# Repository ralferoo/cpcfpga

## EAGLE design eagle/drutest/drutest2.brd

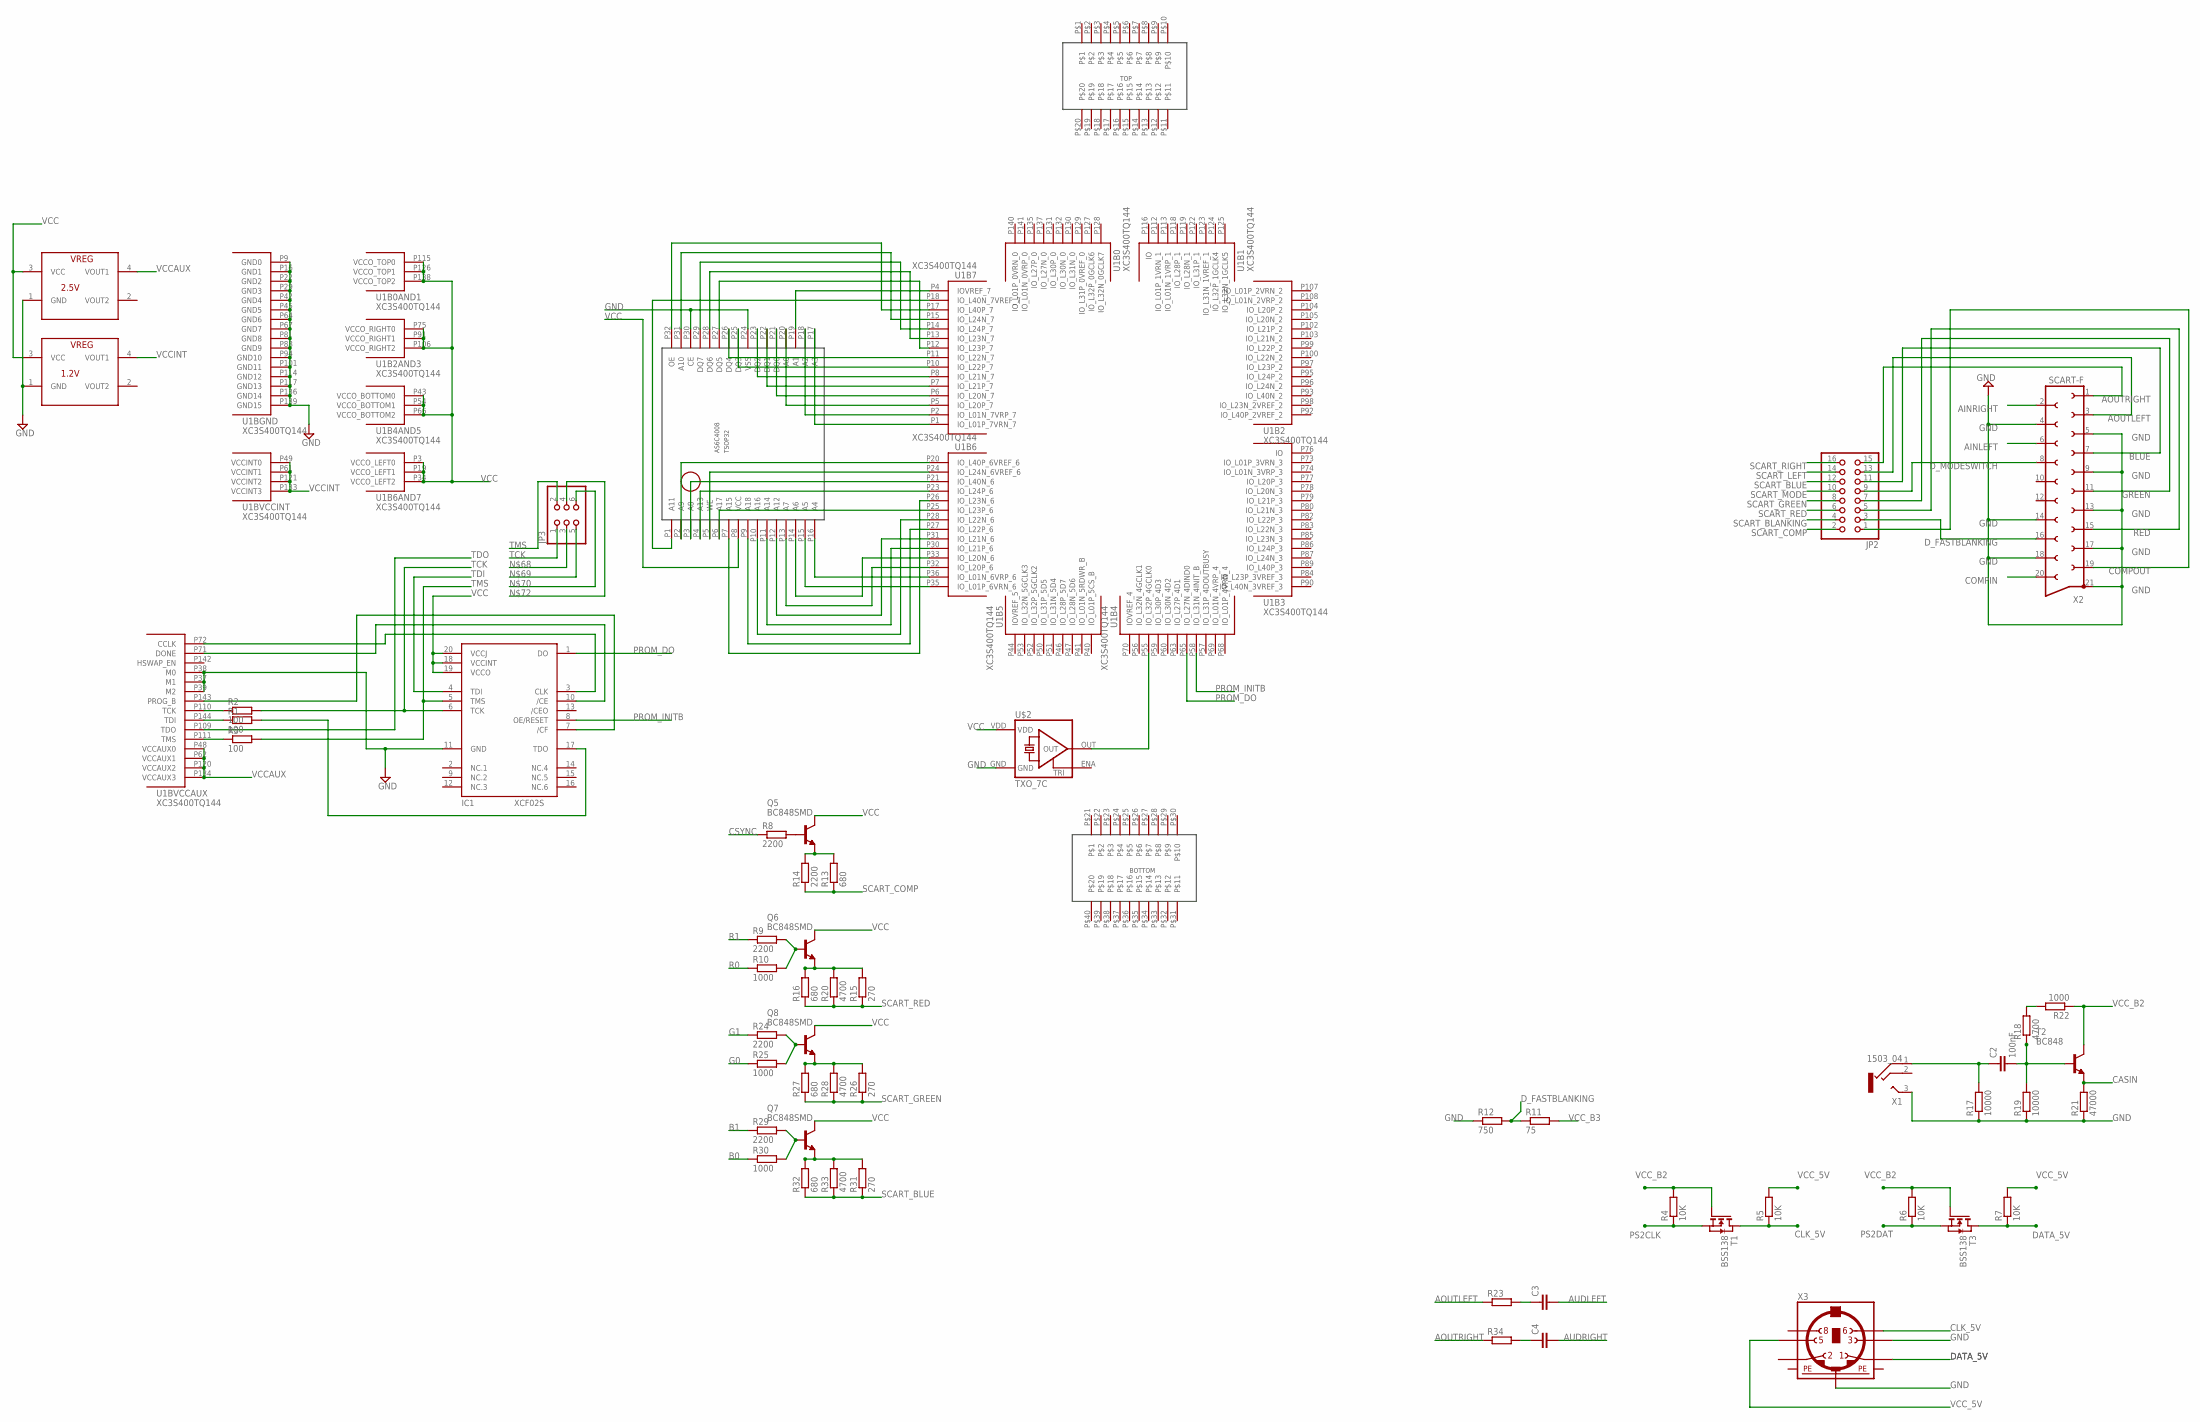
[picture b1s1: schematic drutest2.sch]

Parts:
C2: 100nF; C0603
C3, C4: C-EUC0603; C0603
IC1: XCF02S; VO20
JP2: PINHD-2X8; 2X08
JP3: PINHD-2X3; 2X03
Q5, Q6, Q7, Q8: BC848SMD; SOT23
R1, R2, R3: 100; R0805
R4, R5, R6, R7: 10K; R0805
R8, R9, R14, R24, R29: 2200; R0805
R10, R22, R25, R30: 1000; R0805
R11: 75; R0805
R12: 750; R0805
R13, R16, R27, R32: 680; R0805
R15, R26, R31: 270; R0805
R17, R19: 10000; R0805
R18, R20, R28, R33: 4700; R0805
R21: 47000; R0805
R23, R34: R-EU_M0805; M0805
T1, T3: BSS138; SOT-23
T2: BC848; SOT23
U1: XC3S400TQ144; TQ144
U$1: AS6C4008; TSOP32
U$2: TXO_7C; OSC_7C
U$3: 2.5V; SOT223
U$4: 1.2V; SOT223
U$5: EXPHDR
X1: 1503_04
X2: SCART-F
X3: MINI_DIN_6; M_DIN6

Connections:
AINLEFT: X2.6
AINRIGHT: X2.2
AOUTLEFT: JP2.13, R23.1, X2.3
AOUTRIGHT: JP2.15, R34.1, X2.1
AUDLEFT: C3.2
AUDRIGHT: C4.2
B0: R30.1
B1: R29.1
BLUE: JP2.11, X2.7
CASIN: R21.2, T2.2 (E)
CLK_5V: R5.1, T1.1 (D), X3.6
COMPIN: X2.20
COMPOUT: JP2.1, X2.19
CSYNC: R8.1
DATA_5V: R7.1, T3.1 (D), X3.1
D_FASTBLANKING: JP2.3, R11.1, R12.2, X2.16
D_MODESWITCH: JP2.9, X2.8
G0: R25.1
G1: R24.1
GND: IC1.11 (GND), R12.1, R17.1, R19.1, R21.1, U1.P9 (GND0), U1.P16 (GND1), U1.P22 (GND2), U1.P29 (GND3), U1.P37 (M1), U1.P38 (M0), U1.P39 (M2), U1.P42 (GND4), U1.P45 (GND5), U1.P64 (GND6), U1.P67 (GND7), U1.P81 (GND8), U1.P88 (GND9), U1.P94 (GND10), U1.P101 (GND11), U1.P114 (GND12), U1.P117 (GND13), U1.P136 (GND14), U1.P139 (GND15), U$1.P24 (VSS), U$1.P30 (CE), U$2.GND, U$3.1 (GND), U$4.1 (GND), X1.3 (2), X2.4, X2.5, X2.9, X2.13, X2.14, X2.17, X2.18, X2.21, X3.3, X3.SH2 (PE2)
GREEN: JP2.7, X2.11
unnamed: U1.P1 (IO_L01P_7VRN_7), U$1.P17 (A3)
unnamed: U1.P2 (IO_L01N_7VRP_7), U$1.P18 (A2)
unnamed: U1.P4 (IOVREF_7), U$1.P19 (A1)
unnamed: U1.P5 (IO_L20P_7), U$1.P20 (A0)
unnamed: U1.P6 (IO_L20N_7), U$1.P21 (DQ0)
unnamed: U1.P7 (IO_L21P_7), U$1.P22 (DQ1)
unnamed: U1.P8 (IO_L21N_7), U$1.P23 (DQ2)
unnamed: U1.P10 (IO_L22P_7), U$1.P25 (DQ3)
unnamed: U1.P11 (IO_L22N_7), U$1.P26 (DQ4)
unnamed: U1.P12 (IO_L23P_7), U$1.P27 (DQ5)
unnamed: U1.P13 (IO_L23N_7), U$1.P28 (DQ6)
unnamed: U1.P14 (IO_L24P_7), U$1.P29 (DQ7)
unnamed: U1.P15 (IO_L24N_7), U$1.P31 (A10)
unnamed: U1.P17 (IO_L40P_7), U$1.P32 (OE)
unnamed: U1.P18 (IO_L40N_7VREF_7), U$1.P1 (A11)
unnamed: U1.P20 (IO_L40P_6VREF_6), U$1.P2 (A9)
unnamed: U1.P21 (IO_L40N_6), U$1.P3 (A8)
unnamed: U1.P23 (IO_L24P_6), U$1.P4 (A13)
unnamed: U1.P24 (IO_L24N_6VREF_6), U$1.P5 (WE)
unnamed: U1.P25 (IO_L23P_6), U$1.P6 (A17)
unnamed: U1.P26 (IO_L23N_6), U$1.P7 (A15)
unnamed: U1.P27 (IO_L22P_6), U$1.P9 (A18)
unnamed: U1.P28 (IO_L22N_6), U$1.P10 (A16)
unnamed: U1.P30 (IO_L21P_6), U$1.P11 (A14)
unnamed: U1.P31 (IO_L21N_6), U$1.P12 (A12)
unnamed: U1.P32 (IO_L20P_6), U$1.P13 (A7)
unnamed: U1.P33 (IO_L20N_6), U$1.P14 (A6)
unnamed: U1.P35 (IO_L01P_6VRN_6), U$1.P15 (A5)
unnamed: U1.P36 (IO_L01N_6VRP_6), U$1.P16 (A4)
unnamed: IC1.3 (CLK), U1.P72 (CCLK)
unnamed: IC1.17 (TDO), R1.2
unnamed: IC1.10 (/CE), U1.P71 (DONE)
unnamed: R2.1, U1.P110 (TCK)
unnamed: IC1.7 (/CF), U1.P143 (PROG_B)
unnamed: R1.1, U1.P144 (TDI)
unnamed: R3.1, U1.P111 (TMS)
unnamed: Q6.1 (B), R9.2, R10.2
unnamed: Q6.2 (E), R15.2, R16.2, R20.2
unnamed: Q8.1 (B), R24.2, R25.2
unnamed: Q8.2 (E), R26.2, R27.2, R28.2
unnamed: Q7.1 (B), R29.2, R30.2
unnamed: Q7.2 (E), R31.2, R32.2, R33.2
unnamed: Q5.2 (E), R13.2, R14.2
unnamed: C2.2, R18.1, R19.2, T2.1 (B)
unnamed: C2.1, R17.2, X1.1
unnamed: R18.2, R22.2
unnamed: Q5.1 (B), R8.2
unnamed: C3.1, R23.2
unnamed: C4.1, R34.2
unnamed: U1.P55 (IO_L32P_4GCLK0), U$2.OUT
PE1: X3.SH1 (PE1)
PE3: X3.SH3 (PE3)
PROM_DO: IC1.1 (DO), U1.P65 (IO_L27N_4DIND0)
PROM_INITB: IC1.8 (OE/RESET), U1.P58 (IO_L31N_4INIT_B)
PS2CLK: R4.1, T1.2 (S)
PS2DAT: R6.1, T3.2 (S)
R0: R10.1
R1: R9.1
RED: JP2.5, X2.15
SCART_BLANKING: JP2.4
SCART_BLUE: JP2.12, R31.1, R32.1, R33.1
SCART_COMP: JP2.2, R13.1, R14.1
SCART_GREEN: JP2.8, R26.1, R27.1, R28.1
SCART_LEFT: JP2.14
SCART_MODE: JP2.10
SCART_RED: JP2.6, R15.1, R16.1, R20.1
SCART_RIGHT: JP2.16
TCK: IC1.6 (TCK), JP3.1, R2.2
TDI: IC1.4 (TDI)
TDO: U1.P109 (TDO)
TMS: IC1.5 (TMS), JP3.2, R3.2
VCC: IC1.18 (VCCINT), IC1.19 (VCCO), IC1.20 (VCCJ), Q5.3 (C), Q6.3 (C), Q7.3 (C), Q8.3 (C), U1.P3 (VCCO_LEFT0), U1.P19 (VCCO_LEFT1), U1.P34 (VCCO_LEFT2), U1.P43 (VCCO_BOTTOM0), U1.P54 (VCCO_BOTTOM1), U1.P66 (VCCO_BOTTOM2), U1.P75 (VCCO_RIGHT0), U1.P91 (VCCO_RIGHT1), U1.P106 (VCCO_RIGHT2), U1.P115 (VCCO_TOP0), U1.P126 (VCCO_TOP1), U1.P138 (VCCO_TOP2), U$1.P8 (VCC), U$2.VDD, U$3.3 (VCC), U$4.3 (VCC)
VCCAUX: U1.P48 (VCCAUX0), U1.P62 (VCCAUX1), U1.P120 (VCCAUX2), U1.P134 (VCCAUX3), U$3.4 (VOUT1)
VCCINT: U1.P49 (VCCINT0), U1.P61 (VCCINT1), U1.P121 (VCCINT2), U1.P133 (VCCINT3), U$4.4 (VOUT1)
VCC_5V: R5.2, R7.2, X3.5
VCC_B2: R4.2, R6.2, R22.1, T1.3 (G), T2.3 (C), T3.3 (G)
VCC_B3: R11.2

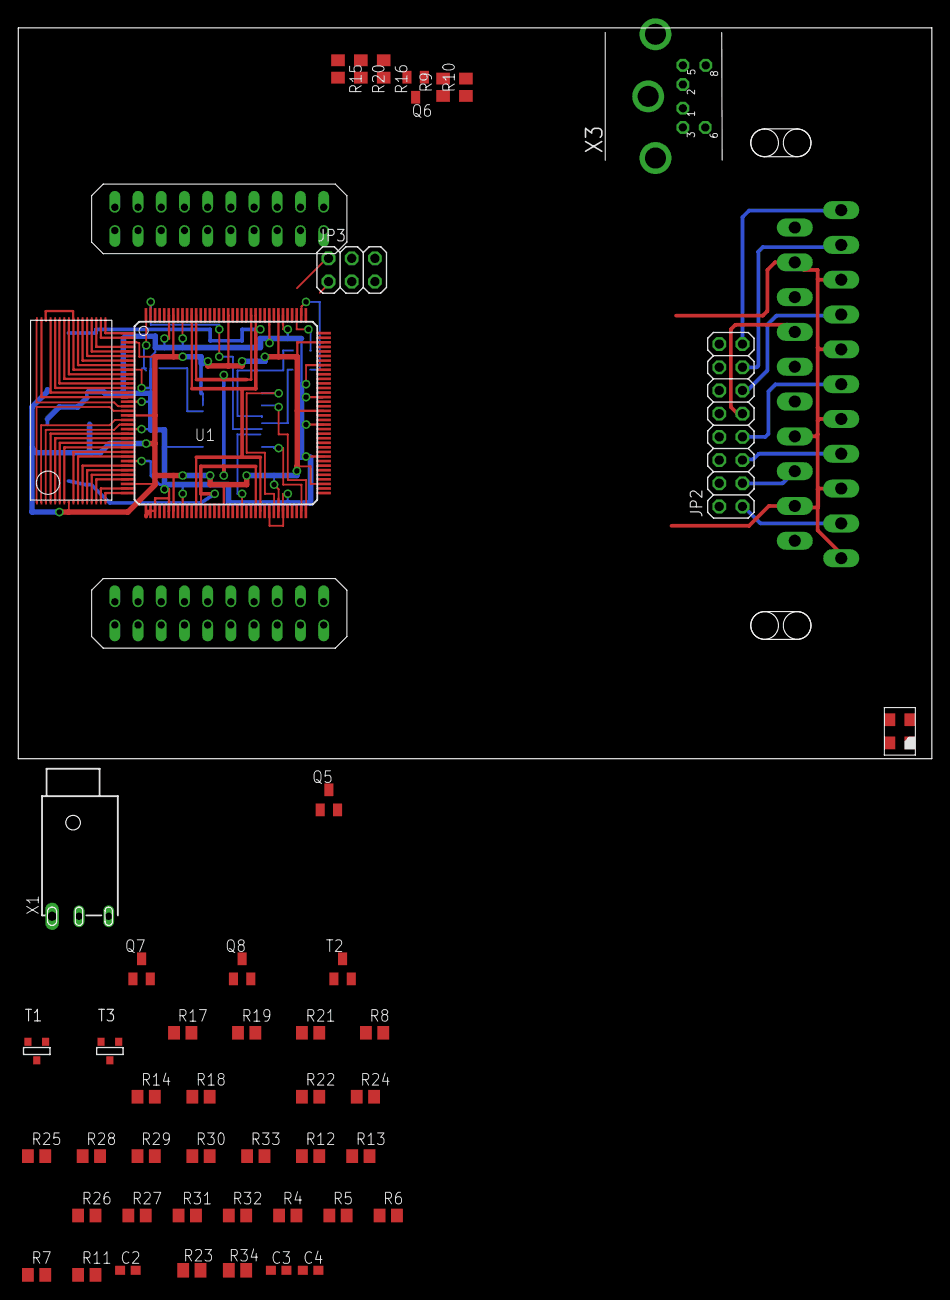
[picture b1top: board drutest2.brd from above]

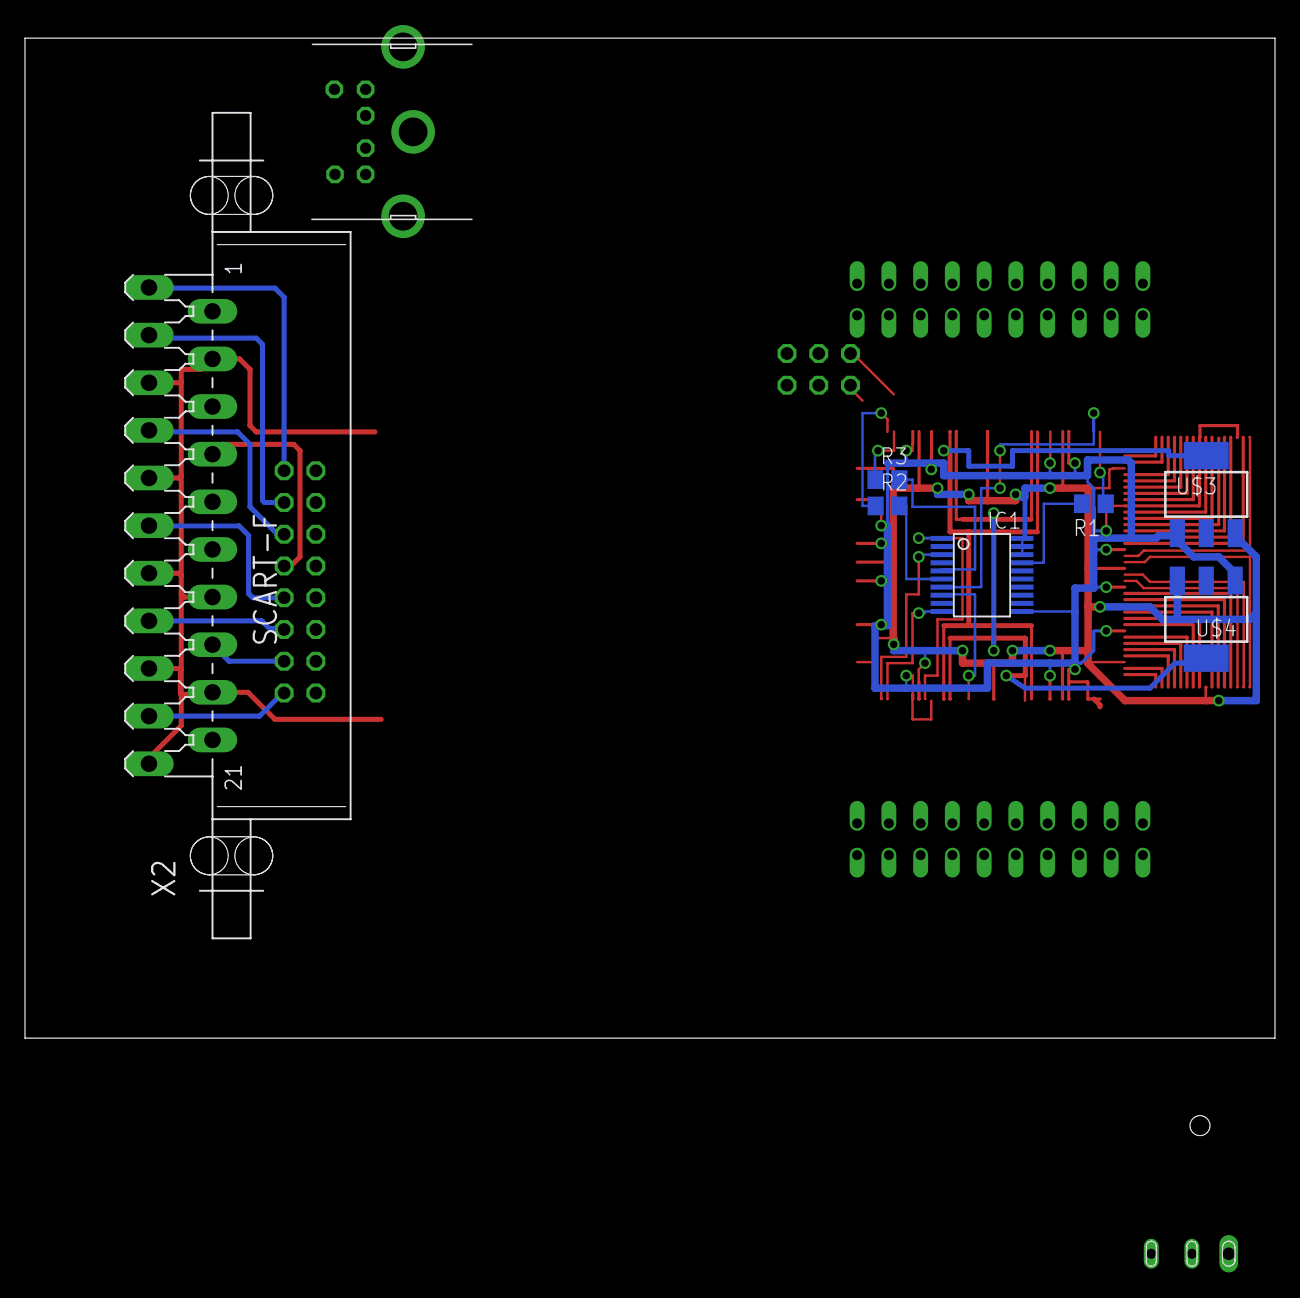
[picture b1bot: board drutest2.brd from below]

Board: 2 copper layers, 100.0 x 98.2 mm, 56 parts (7 on the bottom side), 77 nets.

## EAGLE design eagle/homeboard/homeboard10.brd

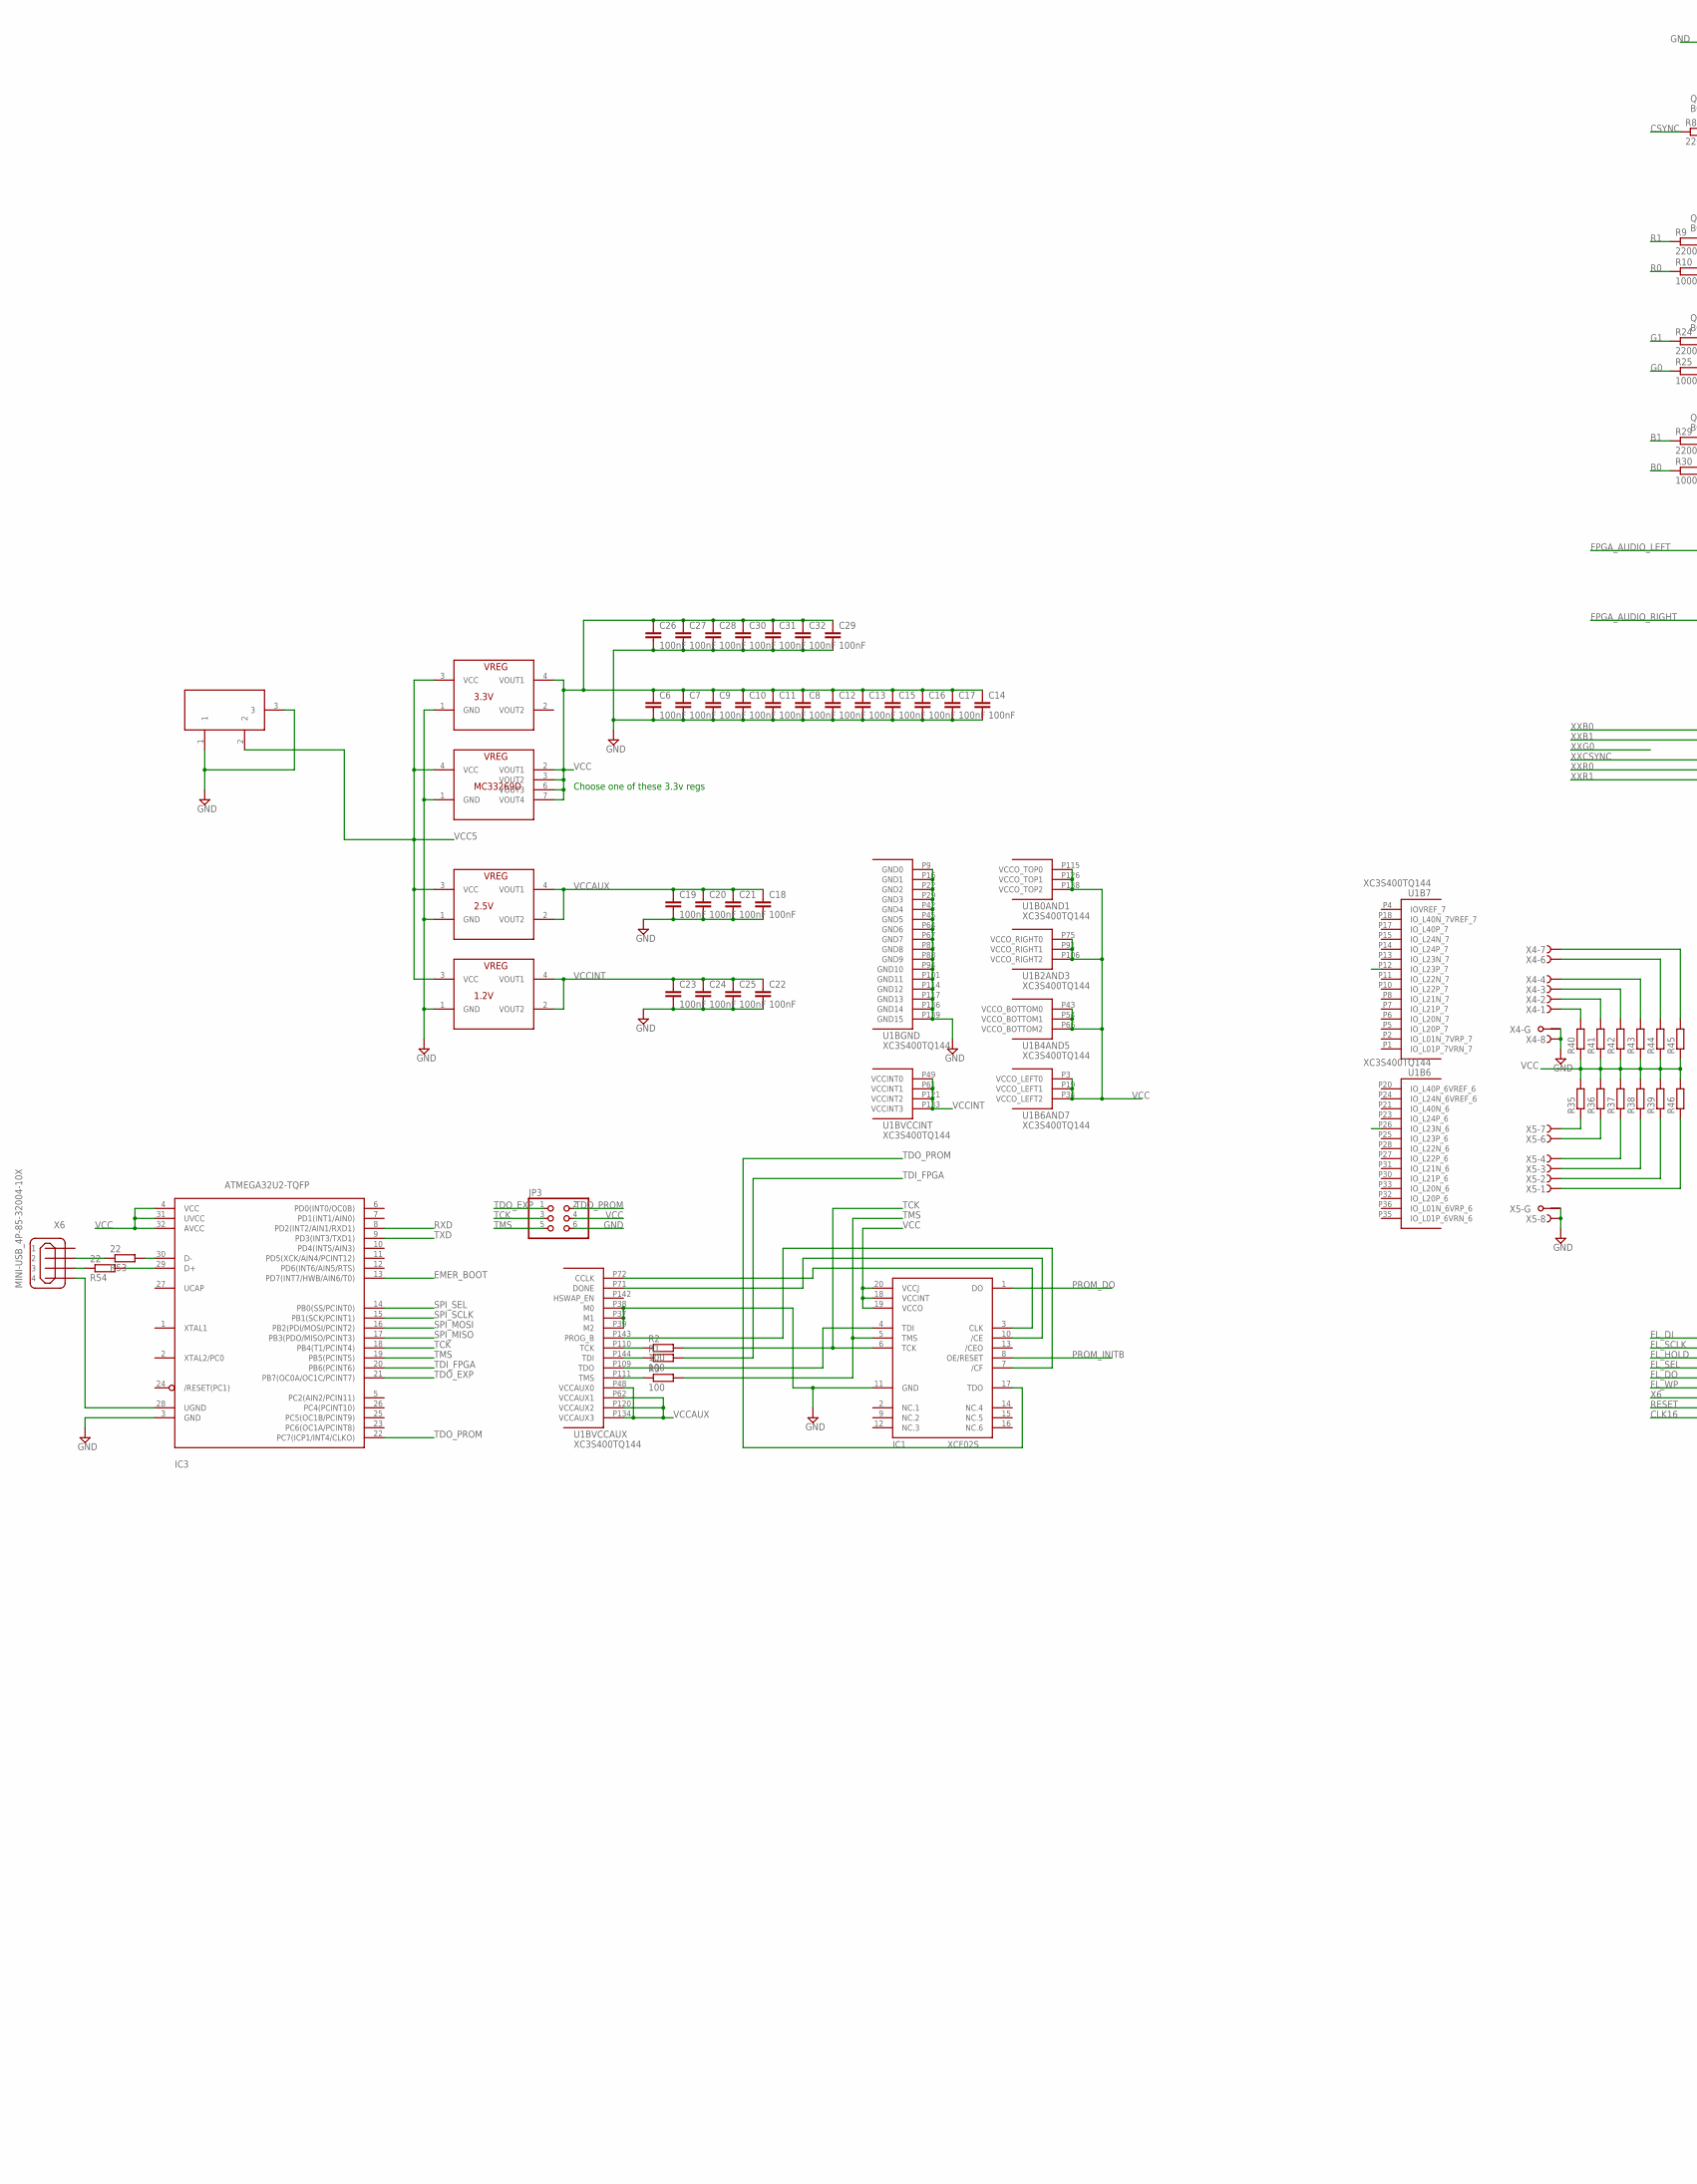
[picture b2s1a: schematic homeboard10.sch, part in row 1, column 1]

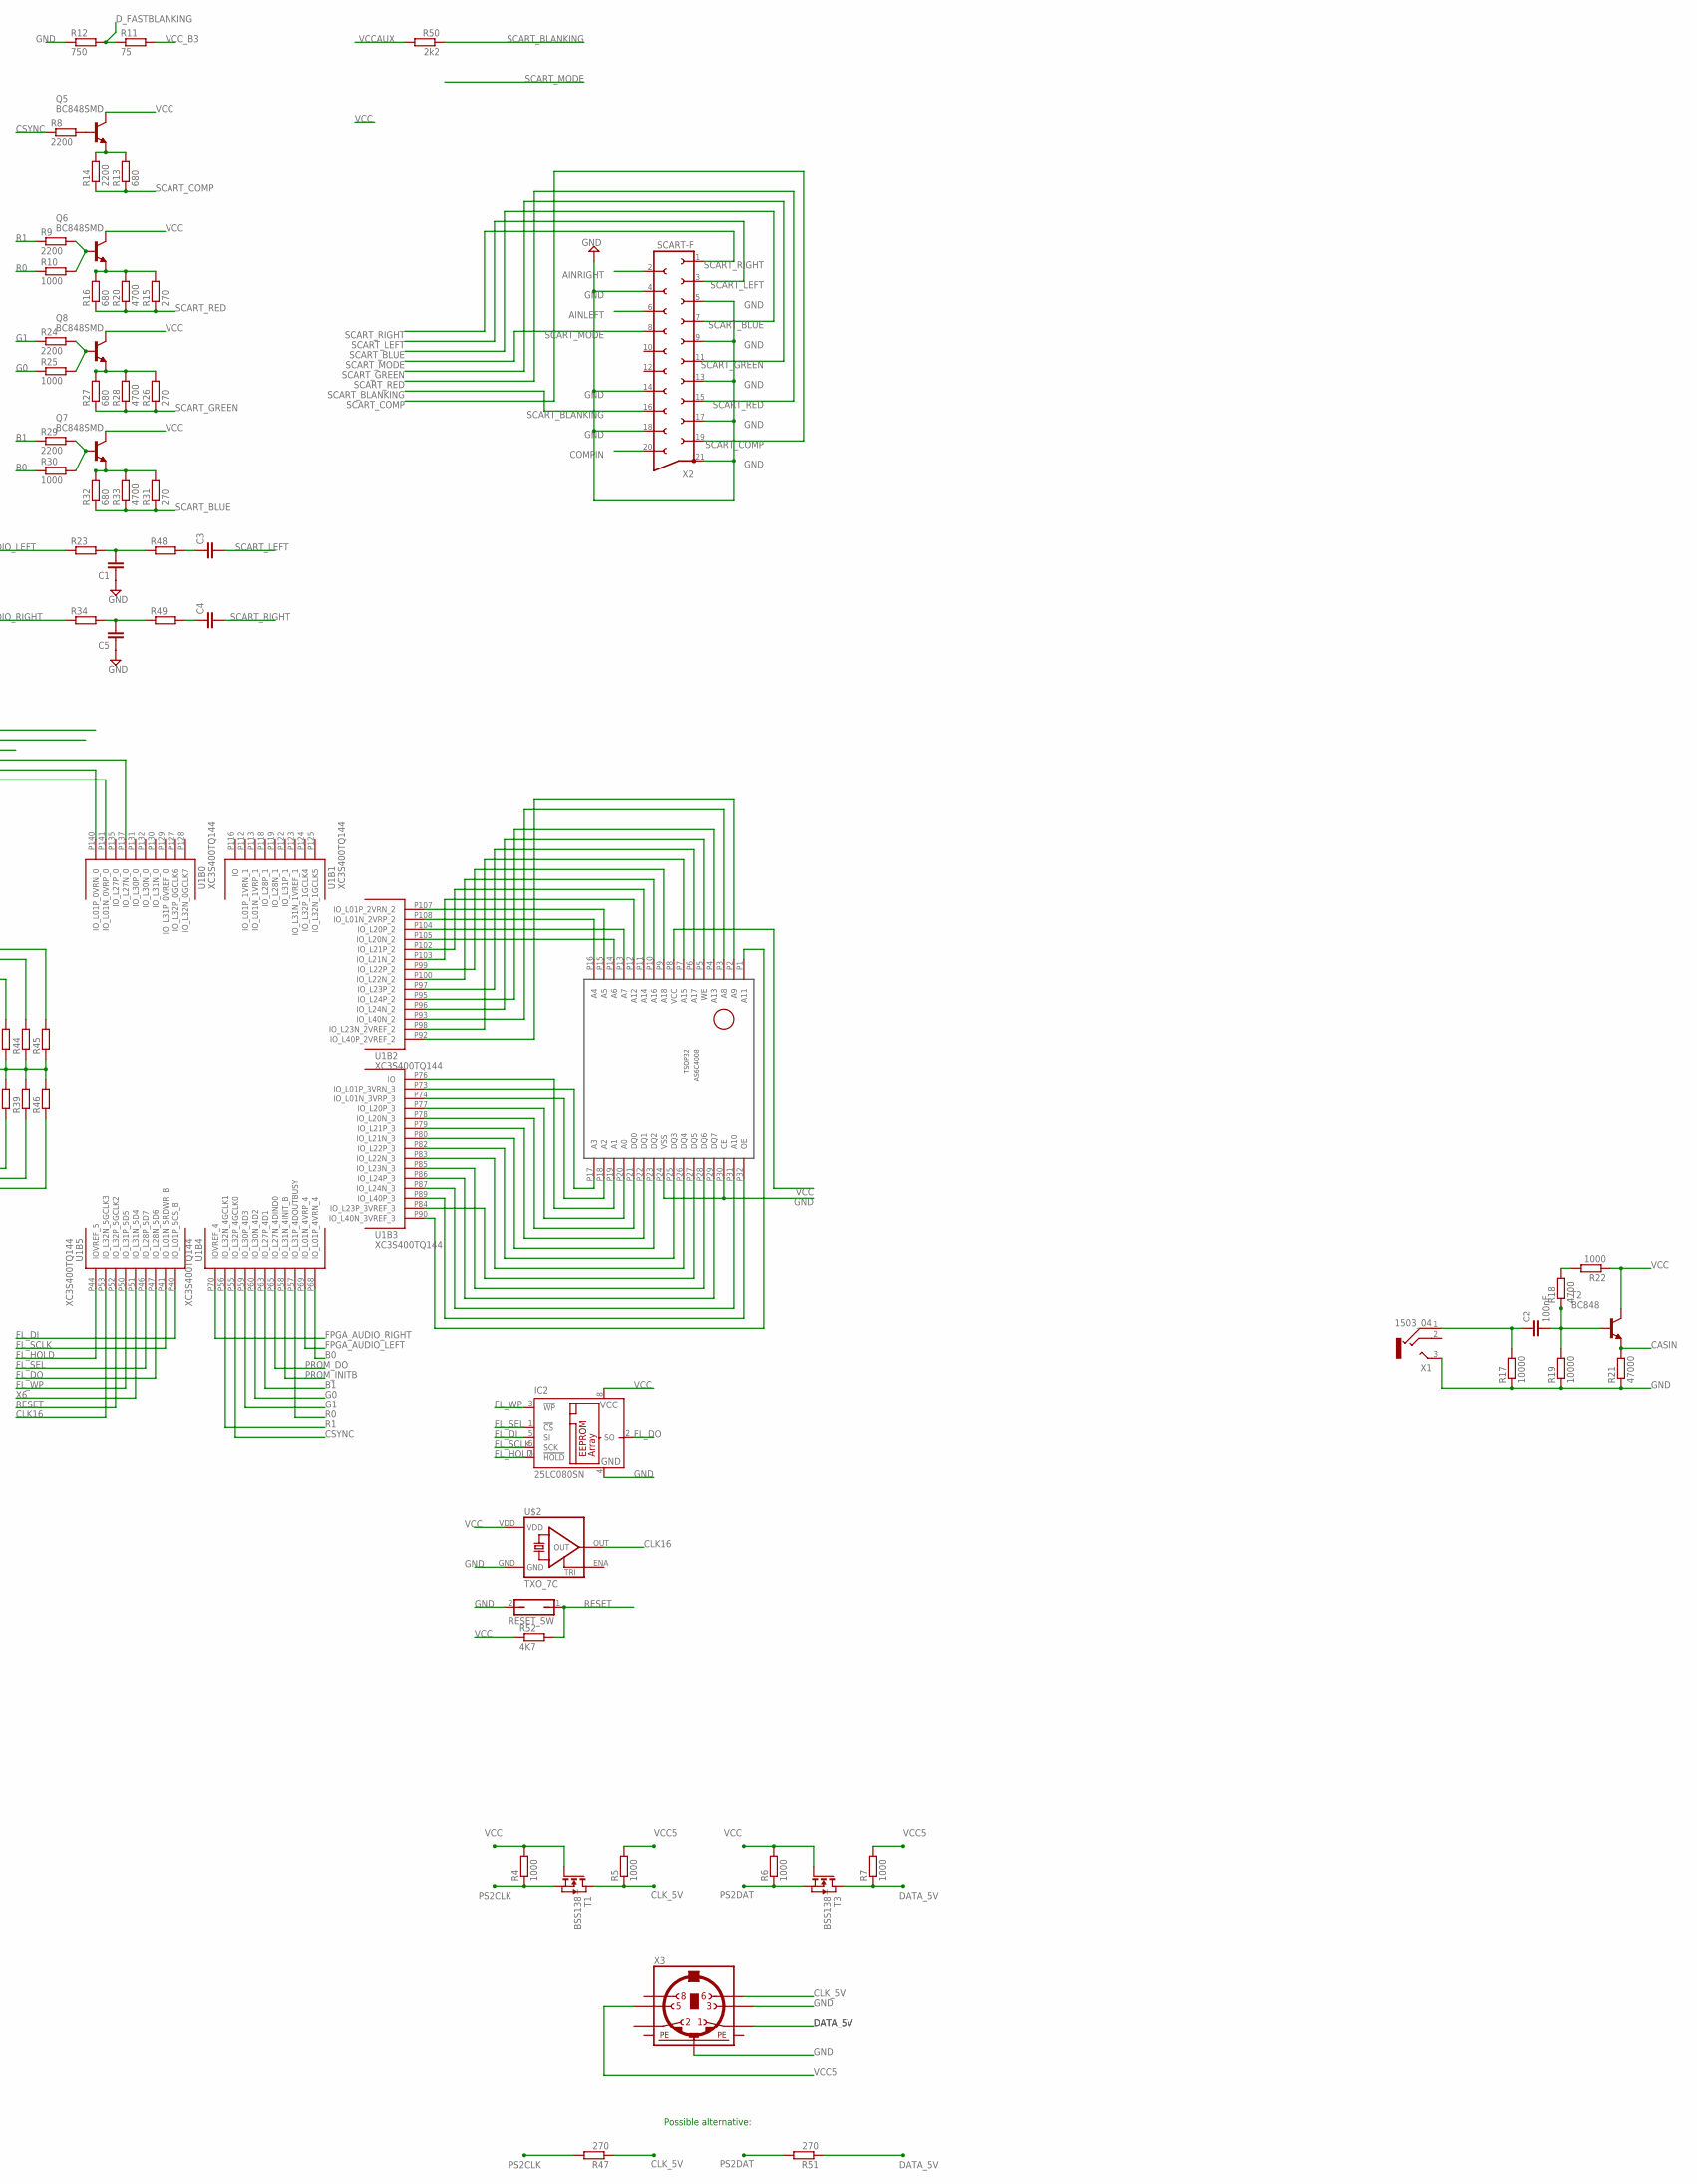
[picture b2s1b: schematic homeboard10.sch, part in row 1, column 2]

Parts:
C1, C3, C4, C5: C-EUC0603; C0603
C2, C6, C7, C8, C9, C10, C11, C12, C13, C14, C15, C16, C17, C18, C19, C20, C21, C22, C23, C24, C25, C26, C27, C28, C29, C30, C31, C32: 100nF; C0603
IC1: XCF02S; VO20
IC2: 25LC080SN; SO-08
IC3: ATMEGA32U2-TQFP; TQFP32-08
JP3: PINHD-2X3; 2X03
Q5, Q6, Q7, Q8: BC848SMD; SOT23
R1, R2, R3: 100; R0805
R4, R5, R6, R7, R10, R22, R25, R30: 1000; R0805
R8, R9, R14, R24, R29: 2200; R0805
R11: 75; R0805
R12: 750; R0805
R13, R16, R27, R32: 680; R0805
R15, R26, R31, R47, R51: 270; R0805
R17, R19: 10000; R0805
R18, R20, R28, R33: 4700; R0805
R21: 47000; R0805
R23, R34, R35, R36, R37, R38, R39, R40, R41, R42, R43, R44, R45, R46, R48, R49: R-EU_M0805; M0805
R50: 2k2; M0805
R52: 4K7; M0805
R53, R54: 22; R0805
REG1.2: 1.2V; SOT223
REG2.5: 2.5V; SOT223
RESET_SW: JP1Q; JP1
T1, T3: BSS138; SOT-23
T2: BC848; SOT23
U1: XC3S400TQ144; TQ144
U$1: AS6C4008; TSOP32
U$2: TXO_7C; OSC_7C
U$3: MC33269D; SO8
U$4: 3.3V; SOT223
X1: 1503_04
X2: SCART-F
X3: MINI_DIN_6; M_DIN6
X4, X5: F09HPS; F09HP
X6: MINI-USB_4P-85-32004-10X; 85-32004-10X
X8: DC21MMX; DC-21MM

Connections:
AINLEFT: X2.6
AINRIGHT: X2.2
B0: R30.1, U1.P68 (IO_L01P_4VRN_4)
B1: R29.1, U1.P63 (IO_L27P_4D1)
CASIN: R21.2, T2.2 (E)
CLK16: U1.P53 (IO_L32N_5GCLK3), U$2.OUT
CLK_5V: R5.1, R47.1, T1.1 (D), X3.6
COMPIN: X2.20
CSYNC: R8.1, U1.P55 (IO_L32P_4GCLK0)
DATA_5V: R7.1, R51.1, T3.1 (D), X3.1
D_FASTBLANKING: R11.1, R12.2
EMER_BOOT: IC3.13 (PD7(INT7/HWB/AIN6/T0))
FL_DI: IC2.5 (SI), U1.P40 (IO_L01P_5CS_B)
FL_DO: IC2.2 (SO), U1.P47 (IO_L28N_5D6)
FL_HOLD: IC2.7 (!HOLD), U1.P44 (IOVREF_5)
FL_SCLK: IC2.6 (SCK), U1.P41 (IO_L01N_5RDWR_B)
FL_SEL: IC2.1 (!CS), U1.P46 (IO_L28P_5D7)
FL_WP: IC2.3 (!WP), U1.P50 (IO_L31P_5D5)
FPGA_AUDIO_LEFT: R23.1, U1.P69 (IO_L01N_4VRP_4)
FPGA_AUDIO_RIGHT: R34.1, U1.P70 (IOVREF_4)
G0: R25.1, U1.P60 (IO_L30N_4D2)
G1: R24.1, U1.P59 (IO_L30P_4D3)
GND: C1.1, C5.1, C6.2, C7.2, C8.2, C9.2, C10.2, C11.2, C12.2, C13.2, C14.2, C15.2, C16.2, C17.2, C18.2, C19.2, C20.2, C21.2, C22.2, C23.2, C24.2, C25.2, C26.2, C27.2, C28.2, C29.2, C30.2, C31.2, C32.2, IC1.11 (GND), IC2.4 (GND), IC3.3 (GND), JP3.6, R12.1, R17.1, R19.1, R21.1, REG1.2.1 (GND), REG2.5.1 (GND), RESET_SW.2, U1.P9 (GND0), U1.P16 (GND1), U1.P22 (GND2), U1.P29 (GND3), U1.P37 (M1), U1.P38 (M0), U1.P39 (M2), U1.P42 (GND4), U1.P45 (GND5), U1.P64 (GND6), U1.P67 (GND7), U1.P81 (GND8), U1.P88 (GND9), U1.P94 (GND10), U1.P101 (GND11), U1.P114 (GND12), U1.P117 (GND13), U1.P136 (GND14), U1.P139 (GND15), U$1.P24 (VSS), U$1.P30 (CE), U$2.GND, U$3.1 (GND), U$4.1 (GND), X1.3 (2), X2.4, X2.5, X2.9, X2.13, X2.14, X2.17, X2.18, X2.21, X3.3, X3.SH2 (PE2), X4.8 (F), X4.G1, X5.8 (F), X5.G1, X8.1, X8.3
unnamed: U1.P108 (IO_L01N_2VRP_2), U$1.P16 (A4)
unnamed: U1.P107 (IO_L01P_2VRN_2), U$1.P15 (A5)
unnamed: U1.P105 (IO_L20N_2), U$1.P14 (A6)
unnamed: U1.P104 (IO_L20P_2), U$1.P13 (A7)
unnamed: U1.P103 (IO_L21N_2), U$1.P12 (A12)
unnamed: U1.P102 (IO_L21P_2), U$1.P11 (A14)
unnamed: U1.P100 (IO_L22N_2), U$1.P10 (A16)
unnamed: U1.P99 (IO_L22P_2), U$1.P9 (A18)
unnamed: U1.P98 (IO_L23N_2VREF_2), U$1.P7 (A15)
unnamed: U1.P97 (IO_L23P_2), U$1.P6 (A17)
unnamed: U1.P96 (IO_L24N_2), U$1.P5 (WE)
unnamed: U1.P95 (IO_L24P_2), U$1.P4 (A13)
unnamed: U1.P93 (IO_L40N_2), U$1.P3 (A8)
unnamed: U1.P92 (IO_L40P_2VREF_2), U$1.P2 (A9)
unnamed: U1.P90 (IO_L40N_3VREF_3), U$1.P1 (A11)
unnamed: U1.P73 (IO_L01P_3VRN_3), U$1.P17 (A3)
unnamed: U1.P74 (IO_L01N_3VRP_3), U$1.P18 (A2)
unnamed: U1.P76 (IO), U$1.P19 (A1)
unnamed: U1.P77 (IO_L20P_3), U$1.P20 (A0)
unnamed: U1.P78 (IO_L20N_3), U$1.P21 (DQ0)
unnamed: U1.P79 (IO_L21P_3), U$1.P22 (DQ1)
unnamed: U1.P80 (IO_L21N_3), U$1.P23 (DQ2)
unnamed: U1.P82 (IO_L22P_3), U$1.P25 (DQ3)
unnamed: U1.P83 (IO_L22N_3), U$1.P26 (DQ4)
unnamed: U1.P84 (IO_L23P_3VREF_3), U$1.P27 (DQ5)
unnamed: U1.P85 (IO_L23N_3), U$1.P28 (DQ6)
unnamed: U1.P86 (IO_L24P_3), U$1.P29 (DQ7)
unnamed: U1.P87 (IO_L24N_3), U$1.P31 (A10)
unnamed: U1.P89 (IO_L40P_3), U$1.P32 (OE)
unnamed: R35.1, X5.7 (F)
unnamed: R36.1, X5.6 (F)
unnamed: R37.1, X5.4 (F)
unnamed: R38.1, X5.3 (F)
unnamed: R39.1, X5.2 (F)
unnamed: IC1.3 (CLK), U1.P72 (CCLK)
unnamed: R53.1, X6.2
unnamed: R46.1, X5.1 (F)
unnamed: IC1.10 (/CE), U1.P71 (DONE)
unnamed: R2.1, U1.P110 (TCK)
unnamed: IC1.7 (/CF), U1.P143 (PROG_B)
unnamed: R40.2, X4.1 (F)
unnamed: R1.1, U1.P144 (TDI)
unnamed: R3.1, U1.P111 (TMS)
unnamed: R41.2, X4.2 (F)
unnamed: R42.2, X4.3 (F)
unnamed: R43.2, X4.4 (F)
unnamed: R44.2, X4.6 (F)
unnamed: R45.2, X4.7 (F)
unnamed: IC3.29 (D+), R54.2
unnamed: C1.2, R23.2, R48.1
unnamed: C3.1, R48.2
unnamed: Q6.1 (B), R9.2, R10.2
unnamed: Q6.2 (E), R15.2, R16.2, R20.2
unnamed: Q8.1 (B), R24.2, R25.2
unnamed: Q8.2 (E), R26.2, R27.2, R28.2
unnamed: Q7.1 (B), R29.2, R30.2
unnamed: Q7.2 (E), R31.2, R32.2, R33.2
unnamed: Q5.2 (E), R13.2, R14.2
unnamed: C2.2, R18.1, R19.2, T2.1 (B)
unnamed: C2.1, R17.2, X1.1
unnamed: R18.2, R22.2
unnamed: Q5.1 (B), R8.2
unnamed: C4.1, R49.2
unnamed: C5.2, R34.2, R49.1
unnamed: R54.1, X6.3
unnamed: IC3.30 (D-), R53.2
unnamed: IC3.28 (UGND), X6.4
PE1: X3.SH1 (PE1)
PE3: X3.SH3 (PE3)
PROM_DO: IC1.1 (DO), U1.P65 (IO_L27N_4DIND0)
PROM_INITB: IC1.8 (OE/RESET), U1.P58 (IO_L31N_4INIT_B)
PS2CLK: R4.1, R47.2, T1.2 (S)
PS2DAT: R6.1, R51.2, T3.2 (S)
R0: R10.1, U1.P57 (IO_L31P_4DOUTBUSY)
R1: R9.1, U1.P56 (IO_L32N_4GCLK1)
RESET: R52.2, RESET_SW.1, U1.P52 (IO_L32P_5GCLK2)
RXD: IC3.8 (PD2(INT2/AIN1/RXD1))
SCART_BLANKING: R50.1, X2.16
SCART_BLUE: R31.1, R32.1, R33.1, X2.7
SCART_COMP: R13.1, R14.1, X2.19
SCART_GREEN: R26.1, R27.1, R28.1, X2.11
SCART_LEFT: C3.2, X2.3
SCART_MODE: X2.8
SCART_RED: R15.1, R16.1, R20.1, X2.15
SCART_RIGHT: C4.2, X2.1
SPI_MISO: IC3.17 (PB3(PDO/MISO/PCINT3))
SPI_MOSI: IC3.16 (PB2(PDI/MOSI/PCINT2))
SPI_SCLK: IC3.15 (PB1(SCK/PCINT1))
SPI_SEL: IC3.14 (PB0(SS/PCINT0))
TCK: IC1.6 (TCK), IC3.18 (PB4(T1/PCINT4)), JP3.3, R2.2
TDI_FPGA: IC3.20 (PB6(PCINT6)), R1.2
TDO_EXP: IC3.21 (PB7(OC0A/OC1C/PCINT7)), JP3.1
TDO_FPGA: IC1.4 (TDI), U1.P109 (TDO)
TDO_PROM: IC1.17 (TDO), IC3.22 (PC7(ICP1/INT4/CLKO)), JP3.2
TMS: IC1.5 (TMS), IC3.19 (PB5(PCINT5)), JP3.5, R3.2
TXD: IC3.9 (PD3(INT3/TXD1))
VCC: C6.1, C7.1, C8.1, C9.1, C10.1, C11.1, C12.1, C13.1, C14.1, C15.1, C16.1, C17.1, C26.1, C27.1, C28.1, C29.1, C30.1, C31.1, C32.1, IC1.18 (VCCINT), IC1.19 (VCCO), IC1.20 (VCCJ), IC2.8 (VCC), IC3.4 (VCC), IC3.31 (UVCC), IC3.32 (AVCC), JP3.4, Q5.3 (C), Q6.3 (C), Q7.3 (C), Q8.3 (C), R4.2, R6.2, R22.1, R35.2, R36.2, R37.2, R38.2, R39.2, R40.1, R41.1, R42.1, R43.1, R44.1, R45.1, R46.2, R52.1, T1.3 (G), T2.3 (C), T3.3 (G), U1.P3 (VCCO_LEFT0), U1.P19 (VCCO_LEFT1), U1.P34 (VCCO_LEFT2), U1.P43 (VCCO_BOTTOM0), U1.P54 (VCCO_BOTTOM1), U1.P66 (VCCO_BOTTOM2), U1.P75 (VCCO_RIGHT0), U1.P91 (VCCO_RIGHT1), U1.P106 (VCCO_RIGHT2), U1.P115 (VCCO_TOP0), U1.P126 (VCCO_TOP1), U1.P138 (VCCO_TOP2), U$1.P8 (VCC), U$2.VDD, U$3.2 (VOUT1), U$3.3 (VOUT2), U$3.6 (VOUT3), U$3.7 (VOUT4), U$4.4 (VOUT1)
VCC5: R5.2, R7.2, REG1.2.3 (VCC), REG2.5.3 (VCC), U$3.4 (VCC), U$4.3 (VCC), X3.5, X8.2
VCCAUX: C18.1, C19.1, C20.1, C21.1, R50.2, REG2.5.2 (VOUT2), REG2.5.4 (VOUT1), U1.P48 (VCCAUX0), U1.P62 (VCCAUX1), U1.P120 (VCCAUX2), U1.P134 (VCCAUX3)
VCCINT: C22.1, C23.1, C24.1, C25.1, REG1.2.2 (VOUT2), REG1.2.4 (VOUT1), U1.P49 (VCCINT0), U1.P61 (VCCINT1), U1.P121 (VCCINT2), U1.P133 (VCCINT3)
VCC_B3: R11.2
X6: U1.P51 (IO_L31N_5D4)
XXCSYNC: U1.P137 (IO_L27N_0)
XXR0: U1.P140 (IO_L01P_0VRN_0)
XXR1: U1.P141 (IO_L01N_0VRP_0)

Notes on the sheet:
Choose one of these 3.3v regs
Possible alternative:
